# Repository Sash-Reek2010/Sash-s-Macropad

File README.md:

# Sash's Macropad
Its a cool tiny keyboard meant to be used to play story based games! It also has an oled to display whatever you want!This is how it would look irl once its finished! 

I think it kinda looks like a calculator but its still insanely cool!!

## Inspo
I really wanted a small macropad so that I could play story based games! I also wanted a cool screen to display random stuff! Plus lights!!!!

## Challenges
This is my first ever time making a pcb and also doing CAD. So it was hard at first but i got the hang of it soon enough! Im really proud of myself tbh :3 

## Features
It has four main keys for wasd and two more for the spacebar and e. It also has an OLED which is nice to have! And a bunch of neopixels for the fun! The outer case is 3d printed and it hosts the pcb inside really well! As for a special feature, holding the space key will translate to esc

## The CAD model
This is my first time designing a model so im really happy with how it turned out! 
It has a tiny window for the XIAO RP2040 because it makes it look cooler! 

## The PCB
I made the PCB in Kicad and it was really fun to make :3

The Schematic!

The PCB! I also included a silkscreen image of my favourite JJBA Character! Im really excited to see it in person!!!!!!

## BOM
- This is everything I used to make it!
- 6x Cherry MX Switches
- 6x DSA Keycaps
- 4x M3x16mm SHCS Bolts
- 6x WS2812B LEDs
- 1x 0.91" 128x32 OLED Display
- 1x XIAO RP2040
- 1x Case (2 3D Printed parts)

## Extras
Making PCBs is insanely fun!!!!!!!!!!!!!!

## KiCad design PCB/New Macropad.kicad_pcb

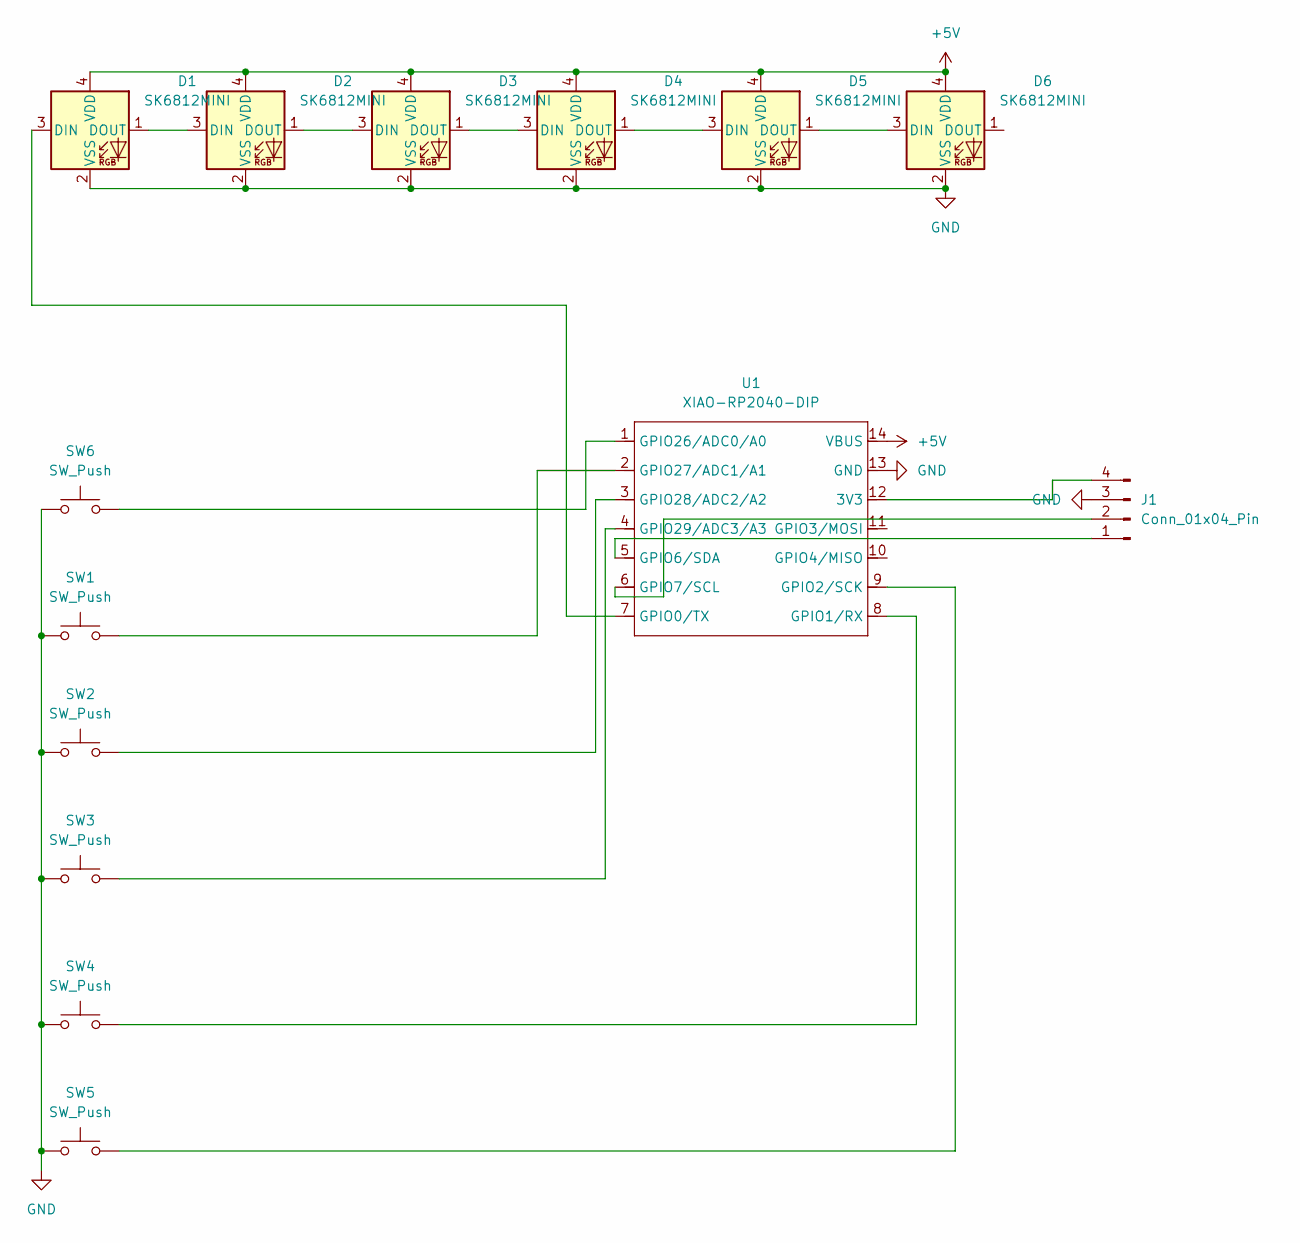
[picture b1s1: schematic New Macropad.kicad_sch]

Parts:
D1, D2, D3, D4, D5, D6: SK6812MINI; LED_SK6812MINI_PLCC4_3.5x3.5mm_P1.75mm
J1: Conn_01x04_Pin; SSD1306-0.91-OLED-4pin-128x32
SW1, SW2, SW3, SW4, SW5, SW6: SW_Push; SW_Cherry_MX_1.00u_PCB
U1: XIAO-RP2040-DIP

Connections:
+5V: D1.4 (VDD), D2.4 (VDD), D3.4 (VDD), D4.4 (VDD), D5.4 (VDD), D6.4 (VDD), U1.14 (VBUS)
GND: D1.2 (VSS), D2.2 (VSS), D3.2 (VSS), D4.2 (VSS), D5.2 (VSS), D6.2 (VSS), J1.3, SW1.1, SW2.1, SW3.1, SW4.1, SW5.1, SW6.1, U1.13 (GND)
unnamed: D1.3 (DIN), U1.7 (GPIO0/TX)
unnamed: D1.1 (DOUT), D2.3 (DIN)
unnamed: D2.1 (DOUT), D3.3 (DIN)
unnamed: D3.1 (DOUT), D4.3 (DIN)
unnamed: D4.1 (DOUT), D5.3 (DIN)
unnamed: D5.1 (DOUT), D6.3 (DIN)
unnamed: J1.1, U1.5 (GPIO6/SDA)
unnamed: J1.2, U1.6 (GPIO7/SCL)
unnamed: J1.4, U1.12 (3V3)
unnamed: SW4.2, U1.8 (GPIO1/RX)
unnamed: SW5.2, U1.9 (GPIO2/SCK)
unnamed: SW6.2, U1.1 (GPIO26/ADC0/A0)
unnamed: SW1.2, U1.2 (GPIO27/ADC1/A1)
unnamed: SW2.2, U1.3 (GPIO28/ADC2/A2)
unnamed: SW3.2, U1.4 (GPIO29/ADC3/A3)

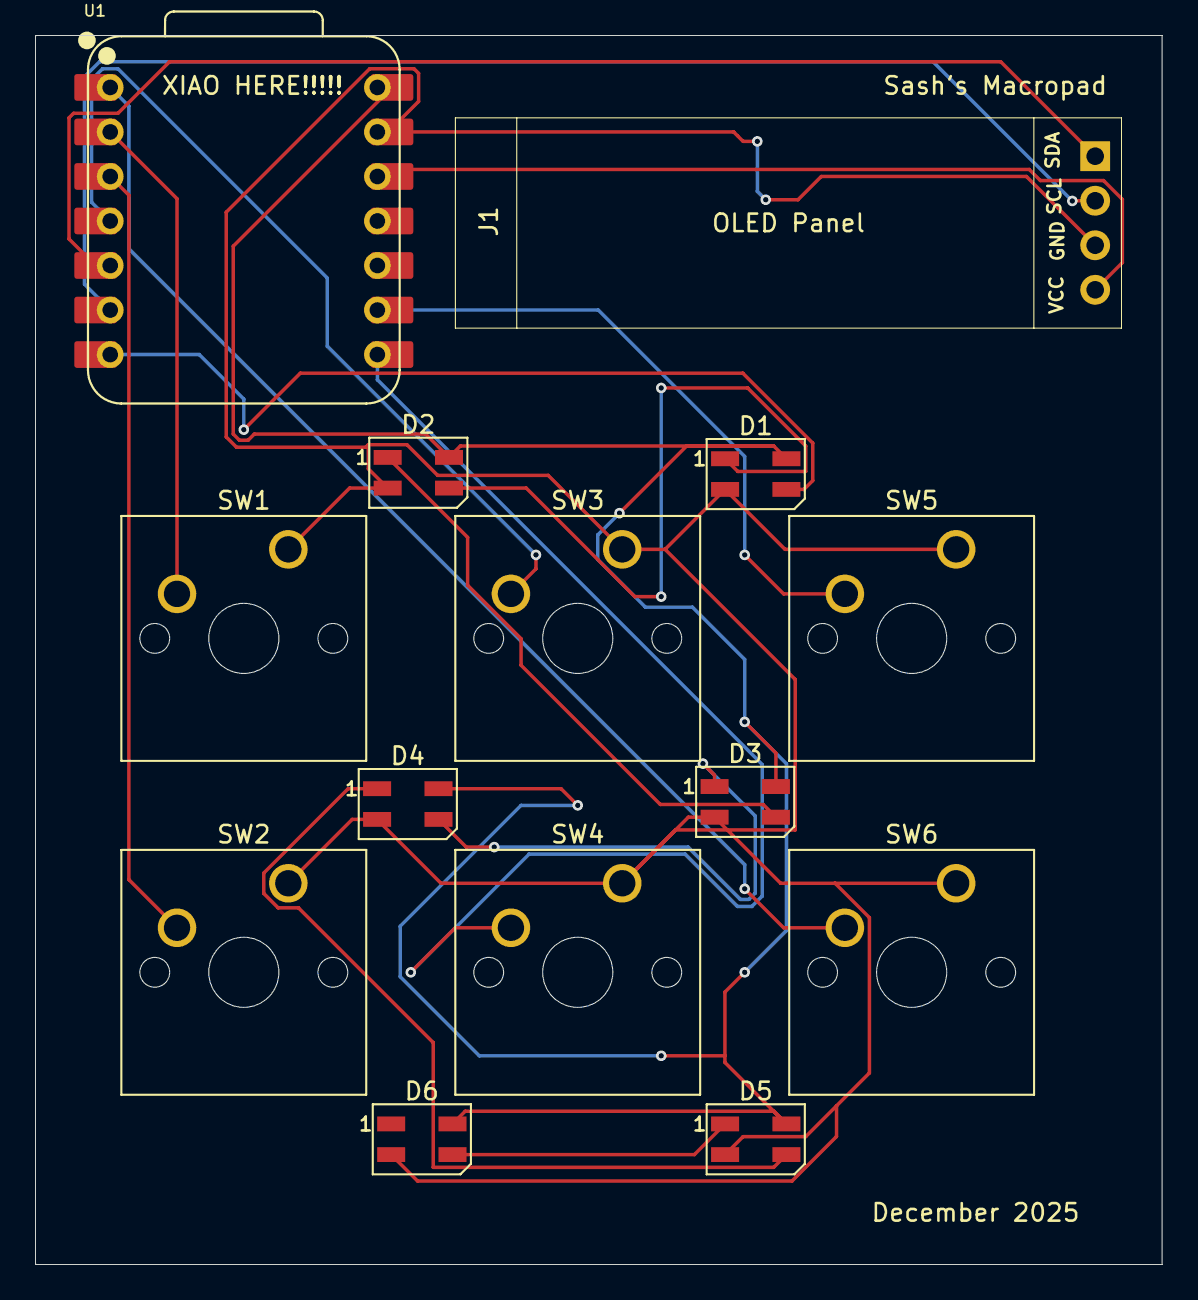
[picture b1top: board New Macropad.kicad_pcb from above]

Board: 2 copper layers, 64.3 x 70.1 mm, 14 parts (0 on the bottom side), 17 nets.

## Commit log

2025-12-08 Add README
2025-12-09 Changed PCB OLED wiring
